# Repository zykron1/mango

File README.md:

# MANGO
An ESP32-S3 based flight computer with an external flash, imu, barometer, magnetometer, 4 servo ports, and 4 pyrotechnic channels with MOSFETs. Designed for Aerospace applications.

## Key Features
 - Dual core Xtensa microcontroller
 - 4 Servo Outputs
 - 4 High current mosfet switches for pyrotechnic channels
 - External 16 MB flash for flight logging
 - IMU, Magnetometer, and Barometer for orientation and state estimation
 - External expansion header with space for an I2C bus, 4 extra GPIO pins, and 2 pairs of power

## Schematic

## PCB

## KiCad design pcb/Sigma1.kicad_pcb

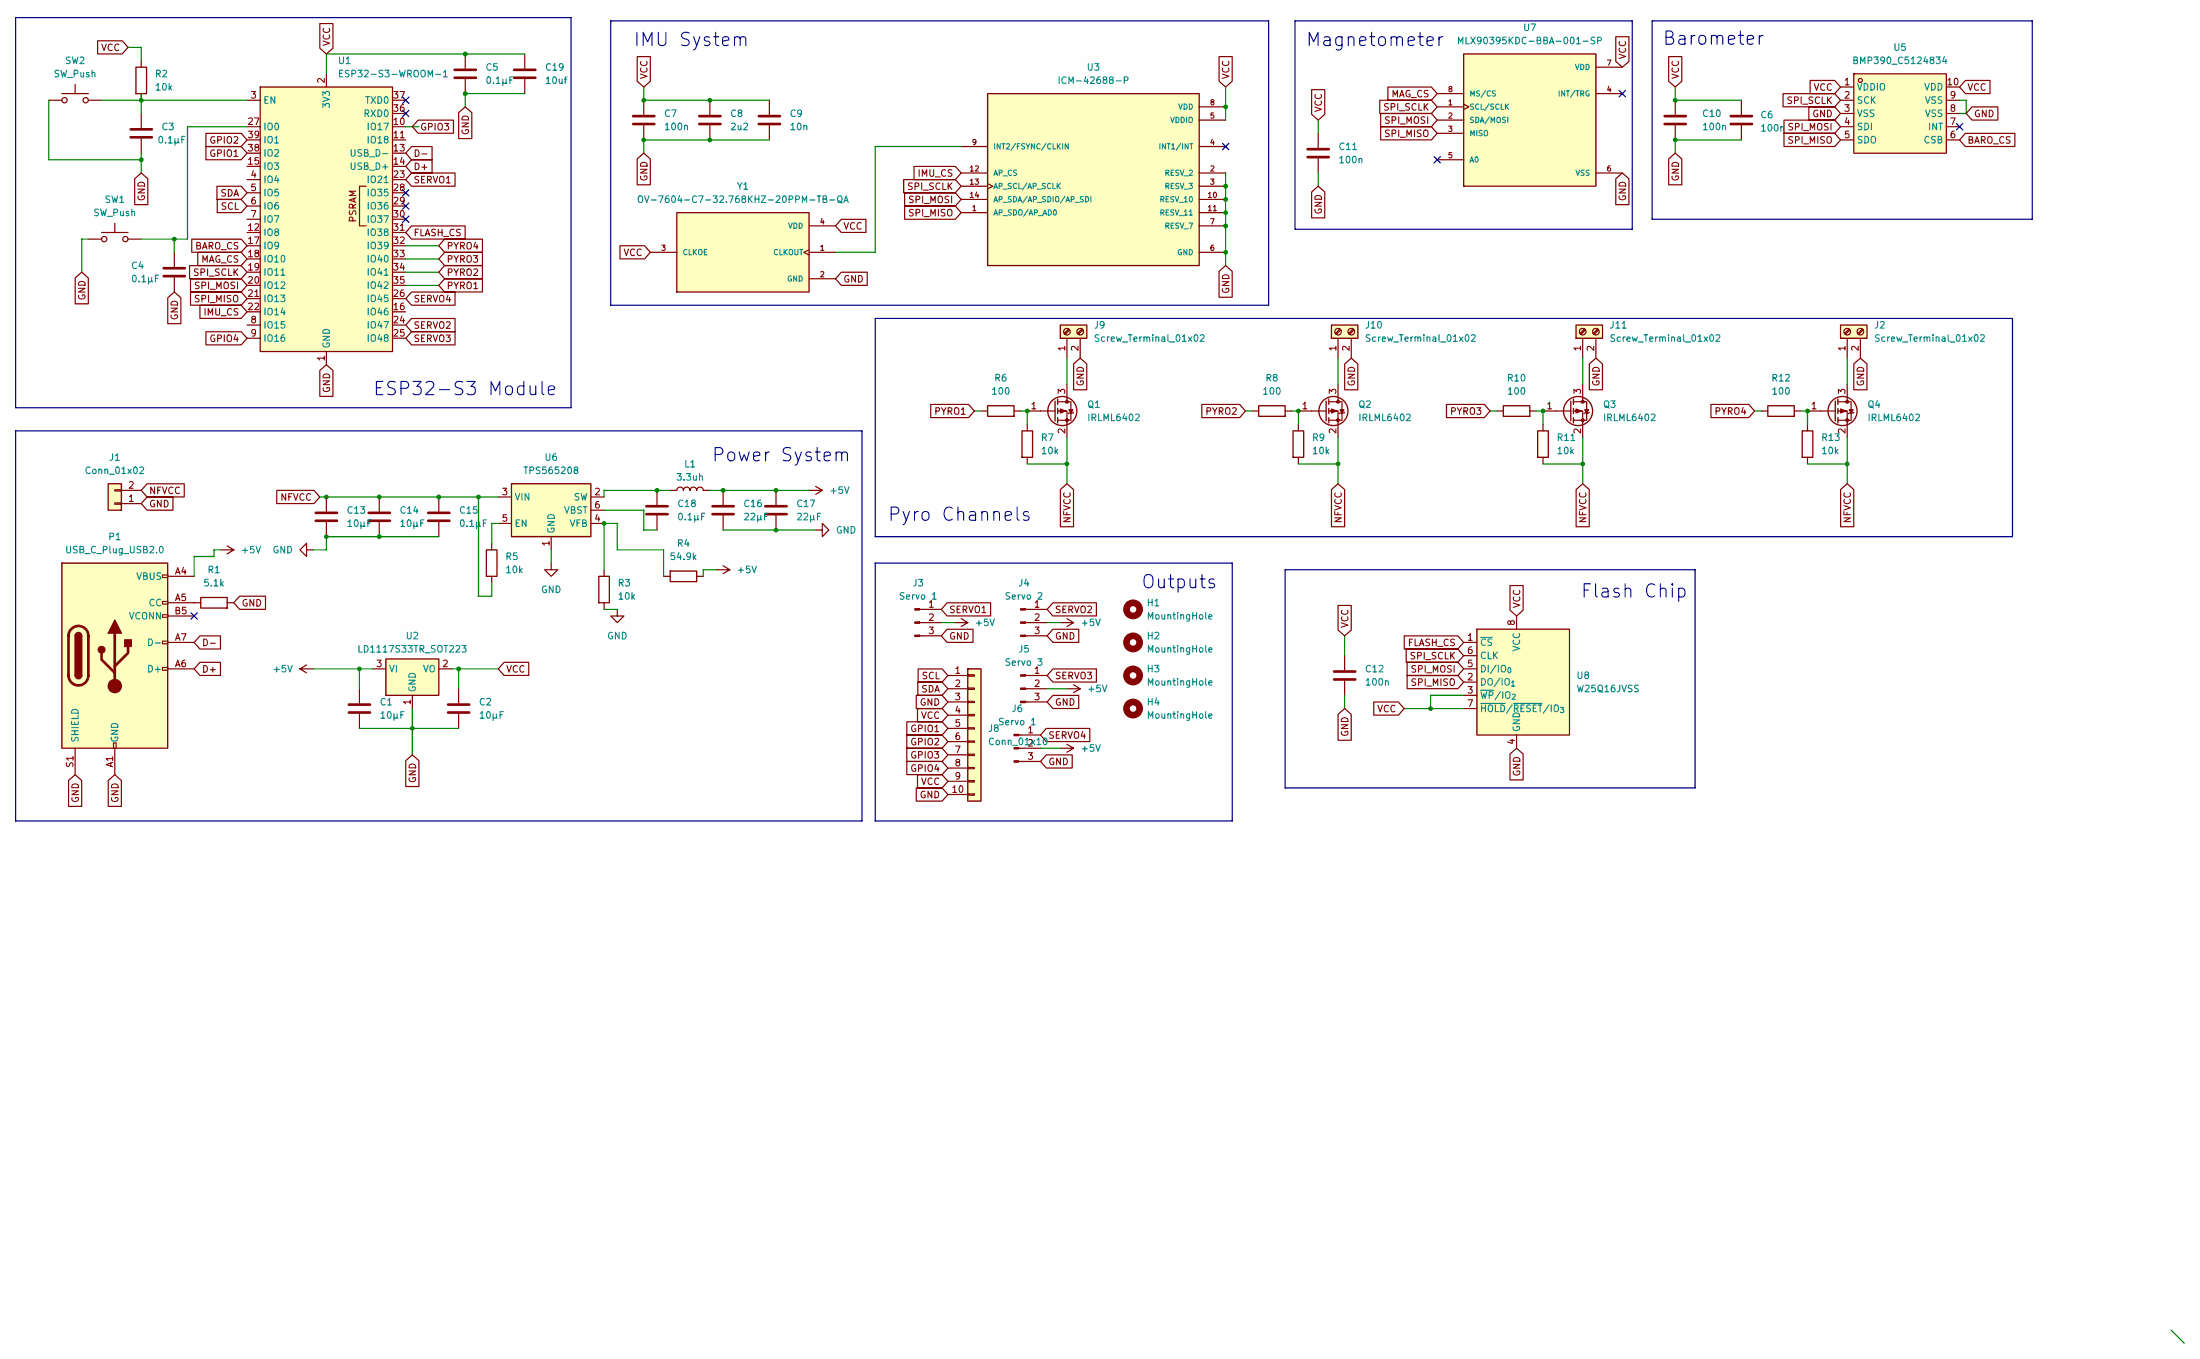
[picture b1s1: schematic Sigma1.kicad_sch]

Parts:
C1, C2, C13, C14: 10µF; C_0603_1608Metric
C3, C4, C15, C18: 0.1µF; C_0603_1608Metric
C5: 0.1μF; C_0603_1608Metric
C6, C7, C10, C11, C12: 100n; C_0603_1608Metric
C8: 2u2; C_0603_1608Metric
C9: 10n; C_0603_1608Metric
C16, C17: 22µF; C_0603_1608Metric
C19: 10uf; C_0603_1608Metric
H1, H2, H3, H4: MountingHole; MountingHole_3.2mm_M3
J1: Conn_01x02; AMASS_XT30U-F_1x02_P5.0mm_Vertical
J2, J9, J10, J11: Screw_Terminal_01x02; TerminalBlock_Xinya_XY308-2.54-2P_1x02_P2.54mm_Horizontal
J3, J6: Servo 1; PinHeader_1x03_P2.54mm_Vertical
J4: Servo 2; PinHeader_1x03_P2.54mm_Vertical
J5: Servo 3; PinHeader_1x03_P2.54mm_Vertical
J8: Conn_01x10; PinHeader_1x10_P2.54mm_Vertical
L1: 3.3uh; L_0805_2012Metric
P1: USB_C_Plug_USB2.0; USB_C_Receptacle_Amphenol_124019772112A
Q1, Q2, Q3, Q4: IRLML6402; SOT-23
R1: 5.1k; R_0603_1608Metric
R2, R7, R9, R11, R13: 10k; R_0603_1608Metric
R3, R5: 10k; R_0603_1608Metric_Pad0.98x0.95mm_HandSolder
R4: 54.9k; R_0603_1608Metric_Pad0.98x0.95mm_HandSolder
R6, R8, R10, R12: 100; R_0603_1608Metric
SW1, SW2: SW_Push; SW_TL3365AF180QG
U1: ESP32-S3-WROOM-1
U2: LD1117S33TR_SOT223; SOT-223-3_TabPin2
U3: ICM-42688-P; PQFN50P300X250X97-14N; PARTREV 1.2
U5: BMP390_C5124834; LGA-10_L2.0-W2.0-P0.50-BL; LCSC Part C5124834
U6: TPS565208; SOT-23-6
U7: MLX90395KDC-BBA-001-SP; SOIC127P600X172-8N; PARTREV 6.0
U8: W25Q16JVSS; SOIC-8_5.3x5.3mm_P1.27mm
Y1: OV-7604-C7-32.768KHZ-20PPM-TB-QA; OSC_OV-7604-C7-32.768KHZ-20PPM-TB-QA; PARTREV 4.4

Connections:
+5V: C1.1, C16.1, C17.1, J3.2, J4.2, J5.2, J6.2, L1.1, P1.A4 (VBUS), P1.A9 (VBUS), P1.B4 (VBUS), P1.B9 (VBUS), R4.1, U2.3 (VI)
BARO_CS: U1.17 (IO9), U5.6 (CSB)
D+: P1.A6 (D+), U1.14 (USB_D+)
D-: P1.A7 (D-), U1.13 (USB_D-)
FLASH_CS: U1.31 (IO38), U8.1 (~CS)
GND: C1.2, C2.2, C3.2, C4.2, C5.2, C6.2, C7.2, C8.2, C9.2, C10.2, C11.2, C12.2, C13.2, C14.2, C15.2, C16.2, C17.2, C19.2, J1.1, J2.2, J3.3, J4.3, J5.3, J6.3, J8.3, J8.10, J9.2, J10.2, J11.2, P1.A1 (GND), P1.A12 (GND), P1.B1 (GND), P1.B12 (GND), P1.S1 (SHIELD), R1.2, R3.2, SW1.1, SW2.1, U1.1 (GND), U1.40 (GND), U1.41 (GND), U2.1 (GND), U3.2 (RESV_2), U3.3 (RESV_3), U3.6 (GND), U3.7 (RESV_7), U3.10 (RESV_10), U3.11 (RESV_11), U5.3 (VSS), U5.8 (VSS), U5.9 (VSS), U6.1 (GND), U7.6 (VSS), U8.4 (GND), Y1.2 (GND)
GPIO1: J8.5, U1.38 (IO2)
GPIO2: J8.6, U1.39 (IO1)
GPIO3: J8.7, U1.10 (IO17)
GPIO4: J8.8, U1.9 (IO16)
IMU_CS: U1.22 (IO14), U3.12 (AP_CS)
MAG_CS: U1.18 (IO10), U7.8 (MS/CS)
NFVCC: C13.1, C14.1, C15.1, J1.2, Q1.2 (S), Q2.2 (S), Q3.2 (S), Q4.2 (S), R5.2, R7.2, R9.2, R11.2, R13.2, U6.3 (VIN)
unnamed: J2.1, Q4.3 (D)
unnamed: J9.1, Q1.3 (D)
unnamed: J10.1, Q2.3 (D)
unnamed: J11.1, Q3.3 (D)
unnamed: P1.A5 (CC), R1.1
unnamed: Q1.1 (G), R6.2, R7.1
unnamed: Q2.1 (G), R8.2, R9.1
unnamed: Q3.1 (G), R10.2, R11.1
unnamed: Q4.1 (G), R12.2, R13.1
unnamed: C3.1, R2.2, SW2.2, U1.3 (EN)
unnamed: C4.1, SW1.2, U1.27 (IO0)
unnamed: U3.9 (INT2/FSYNC/CLKIN), Y1.1 (CLKOUT)
unnamed: R5.1, U6.5 (EN)
unnamed: C18.1, L1.2, U6.2 (SW)
unnamed: C18.2, U6.6 (VBST)
unnamed: R3.1, R4.2, U6.4 (VFB)
PYRO1: R6.1, U1.35 (IO42)
PYRO2: R8.1, U1.34 (IO41)
PYRO3: R10.1, U1.33 (IO40)
PYRO4: R12.1, U1.32 (IO39)
SCL: J8.1, U1.6 (IO6)
SDA: J8.2, U1.5 (IO5)
SERVO1: J3.1, U1.23 (IO21)
SERVO2: J4.1, U1.24 (IO47)
SERVO3: J5.1, U1.25 (IO48)
SERVO4: J6.1, U1.26 (IO45)
SPI_MISO: U1.21 (IO13), U3.1 (AP_SDO/AP_AD0), U5.5 (SDO), U7.3 (MISO), U8.2 (DO/IO_{1})
SPI_MOSI: U1.20 (IO12), U3.14 (AP_SDA/AP_SDIO/AP_SDI), U5.4 (SDI), U7.2 (SDA/MOSI), U8.5 (DI/IO_{0})
SPI_SCLK: U1.19 (IO11), U3.13 (AP_SCL/AP_SCLK), U5.2 (SCK), U7.1 (SCL/SCLK), U8.6 (CLK)
VCC: C2.1, C5.1, C6.1, C7.1, C8.1, C9.1, C10.1, C11.1, C12.1, C19.1, J8.4, J8.9, R2.1, U1.2 (3V3), U2.2 (VO), U3.5 (VDDIO), U3.8 (VDD), U5.1 (VDDIO), U5.10 (VDD), U7.7 (VDD), U8.3 (~WP/IO_{2}), U8.7 (~HOLD/~RESET/IO_{3}), U8.8 (VCC), Y1.3 (CLKOE), Y1.4 (VDD)

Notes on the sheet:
ESP32-S3 Module
Flash Chip
Magnetometer
Outputs
Pyro Channels
Power System
Barometer
IMU System

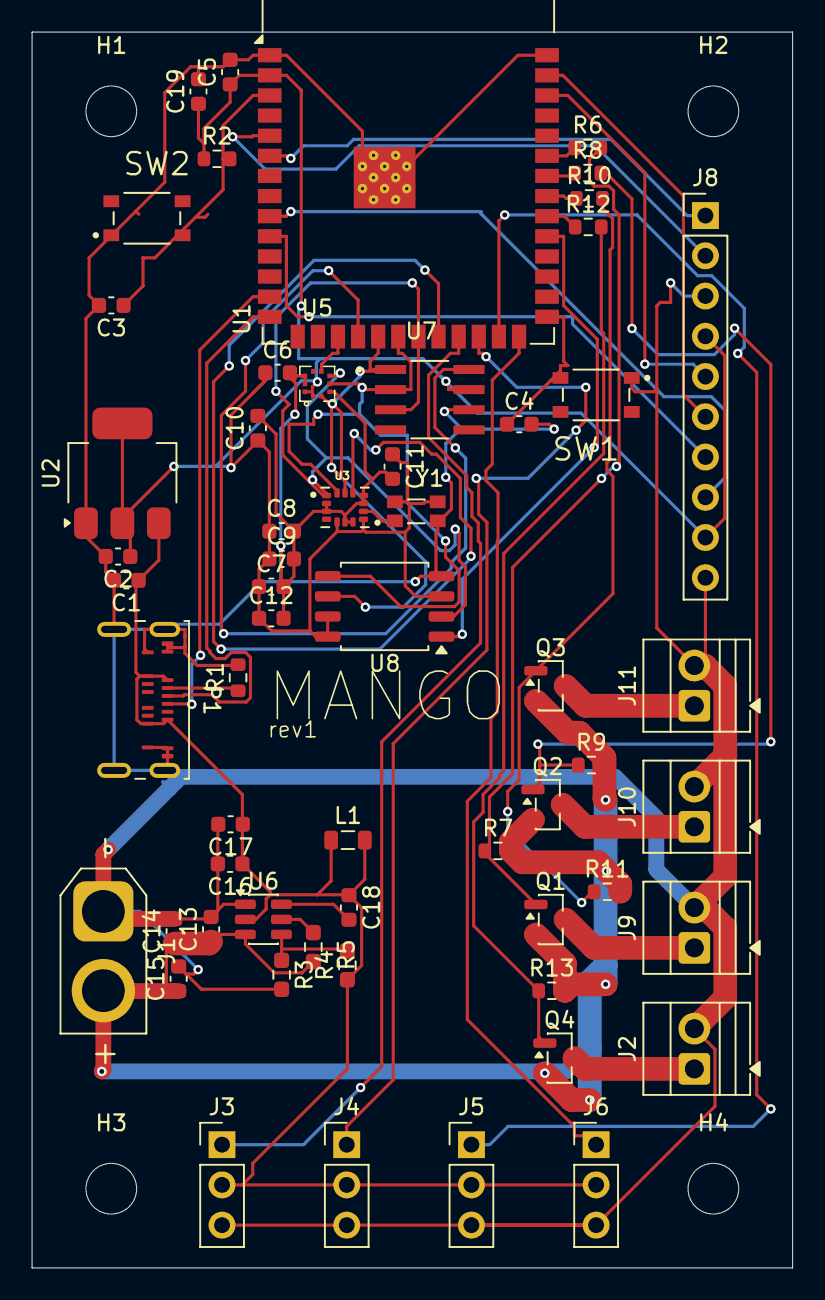
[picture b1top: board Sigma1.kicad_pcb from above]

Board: 2 copper layers, 48.0 x 78.0 mm, 62 parts (0 on the bottom side), 43 nets.

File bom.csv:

Product ,Link,Cost Per Item,Quantity,Total,Note
(pcb AND STENCIL),https://github.com/zykron1/mango/blob/main/pcb/production/MA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,$19.53,1,$16.17,
10µF,https://www.digikey.com/en/products/detail/murata-electronic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,$0.25,4,$1.00,
100n,https://www.digikey.com/en/products/detail/murata-electronic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,$0.25,5,$1.25,
0.1µF,https://www.digikey.com/en/products/detail/murata-electronic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,$0.25,5,$1.25,
22µF,https://www.digikey.com/en/products/detail/yageo/CC0603MRX5R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,$0.65,2,$1.30,
10uf,https://www.digikey.com/en/products/detail/murata-electronic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,$0.25,1,$0.25,
2u2,https://www.digikey.com/en/products/detail/samsung-electro-m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,$0.08,1,$0.08,
10n,https://www.digikey.com/en/products/detail/murata-electronic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,$0.14,1,$0.14,
Conn_01x02,https://www.digikey.com/en/products/detail/amphenol-icc-fci-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,$0.30,1,$0.30,
Screw_Terminal_01x02,https://tinkersphere.com/breadboard-perfboard-prototyping/47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,$0.75,4,$3.00,Not requesting Funding for this
Servo 1,sharing from 10,,2,0,
Servo 2,sharing from 10,,1,0,
Servo 3,sharing from 10,,1,0,
Conn_01x10,sharing from 10,,1,0,
USB_C_Plug_USB2.0,https://www.digikey.com/en/products/detail/amphenol-cs-comme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,$1.96,1,$1.96,
IRLML6402,https://www.digikey.com/en/products/detail/infineon-technolo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,$0.42,4,$1.68,
5.1k,https://www.digikey.com/en/products/detail/yageo/RC0603FR-10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,$0.10,1,$0.10,
100,https://www.digikey.com/en/products/detail/yageo/RC0603FR-10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,$0.10,4,$0.40,
<<<<<<< HEAD
10k,https://www.digikey.com/en/products/detail/yageo/RC0603FR-10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,$0.10,6,$0.60,
60,https://www.digikey.com/en/products/detail/bourns-inc/CR0603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,$0.10,1,$0.10,
330,https://www.digikey.com/en/products/detail/vishay-dale/CRCW0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,$0.10,1,$0.10,
=======
10k,https://www.digikey.com/en/products/detail/yageo/RC0603FR-10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,$0.10,7,$0.70,
3.3uh,https://www.digikey.com/en/products/detail/murata-electronic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,$0.17,1,$0.17,
54.9k,https://www.digikey.com/en/products/detail/yageo/RC0603FR-07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,$0.10,1,$0.10,
>>>>>>> d75fabc (added inductor and used recomended texas instruments resistors)
TS-1088R-02026,https://www.digikey.com/en/products/detail/e-switch/TL3365AF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,$0.21,2,$0.42,
ESP32-S3-WROOM-1,https://www.digikey.com/en/products/detail/espressif-systems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,$5.49,1,$5.49,
LD1117S33TR_SOT223,https://www.digikey.com/en/products/detail/stmicroelectronic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,$0.34,1,$0.34,
ICM-42688-P,https://www.digikey.com/en/products/detail/tdk-invensense/IC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,$4.67,1,$4.67,
BMP390_C5124834,https://www.digikey.com/en/products/detail/bosch-sensortec/B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,$3.15,1,$3.15,
TPS565208,https://www.digikey.com/en/products/detail/texas-instruments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,$1.38,1,$1.38,
MLX90395KDC-BBA-001-SP,https://www.digikey.com/en/products/detail/melexis-technolog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,$2.85,1,$2.85,
W25Q16JVSS,https://www.digikey.com/en/products/detail/winbond-electroni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,$0.60,1,$0.60,
OV-7604-C7-32.768KHZ-20PPM-TB-QA,https://www.digikey.com/en/products/detail/micro-crystal-ag/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,$2.07,1,$2.07,
Subtotal,$50.65,,,,
DigiKey Shipping Cost,$6.99,,,,
Digikey Tarrif Cost,$0.80,,,,
Total Parts Cost,$42.41,(TAXES),,,
Total Board Cost,$58.58,,,,
Asking For: 62 dollars(JLC prices are variable),,,,,

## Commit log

2025-12-31 supply chain changes
2025-12-31 drc fixes
2025-12-31 BOM + supply chain changes
2026-01-01 final commit
2026-01-02 better image
2026-01-03 extremely rought basic firmware for drone with MMU, pid, and sensor loop control. arduino cpp
2026-01-03 Revise bom.csv with updated product details
    Updated bill of materials with new links and costs.
2026-01-03 fixed price
2026-01-25 fix conflict?
